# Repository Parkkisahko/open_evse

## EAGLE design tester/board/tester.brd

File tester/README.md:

# Basics
This testing library contains both an Arduino sketch, an example schema and python test cases to test relay and PWM timings to match 

# Python tests
## Setup
- Install pip first. ´sudo apt-get install python3-pip´
- Setup virtual environment: ´virtualenv -p python3 _py_env´
- Activate virtual environment: ´source _py_env/bin/activate´
- Install packages: ´pip install -r requirements.txt´

## Running tests
- Identify the serial ports used for both Arduino (testing device) and OpenEVSE
-- On OS X and Linux: ´ls /dev/tty*´
-- Replace OPEN_EVSE_PORT and TESTER_PORT with the correct ports in test.py
- Run tests by entering ´python test.py´

## Test cases
- TBD

# OpenEVSE tester
## Notes
- The schema provided is sensitive to board voltage due to selected optocoupler components not fully saturating at voltages below 5 V
- To overcome this issue, use a separate power supply for the Arduino

## Possible improvements
- Change optos to transistors
- Measure voltage at PWM high and low state
- Add circuits and corresponding code to provide for following automated test cases:
-- Diode check fail
-- Ground check fail
-- Stuck relay check (NOTE: Requires high voltages on board!)

# License
Open EVSE tester is licensed under the GNU license.
Copyright 2019 Santeri Oksanen / Parking Energy Ltd

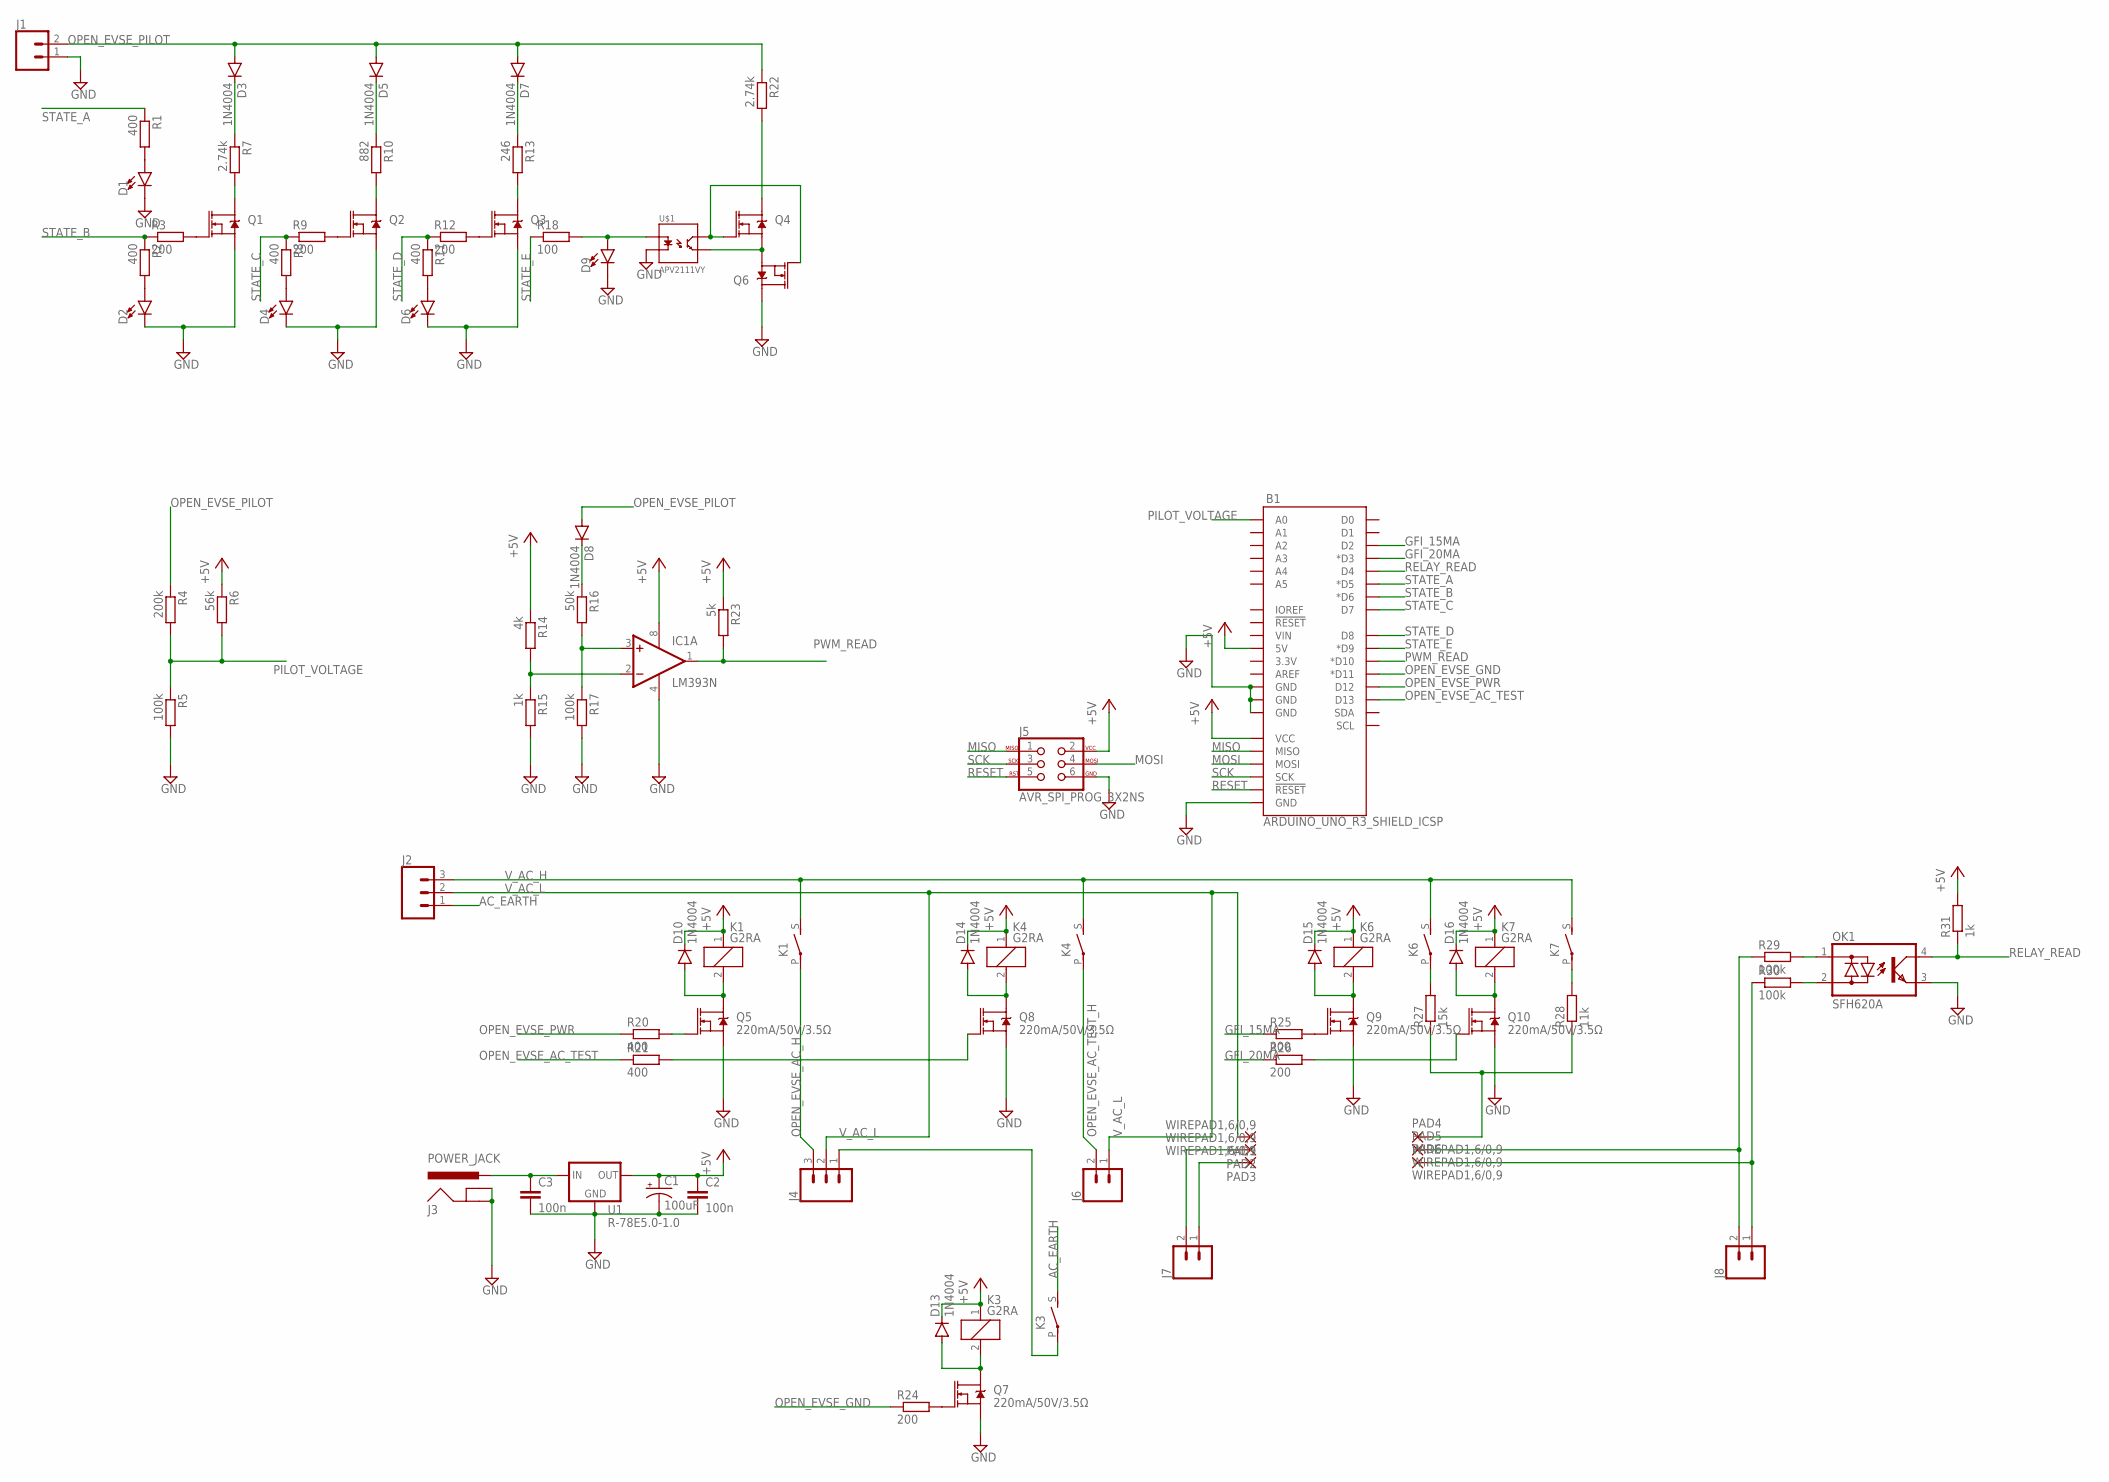
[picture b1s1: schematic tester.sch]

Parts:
B1: ARDUINO_UNO_R3_SHIELD_ICSP; UNO_R3_SHIELD_ICSP
C1: 100uF; CPOL-RADIAL-2.5MM-6.5MM
C2, C3: 100n; C025-024X044
D1, D2, D4, D6, D9: LED-FKIT-1206; FKIT-LED-1206
D3, D5, D7, D8, D10, D13, D14, D15, D16: 1N4004; DO41-10
IC1: LM393N; DIL08
J1, J6, J7, J8: CONN_023.5MM; SCREWTERMINAL-3.5MM-2
J2, J4: CONN_03-SCREW-5MM; SCREWTERMINAL-5MM-3
J3: POWER_JACK; POWER_JACK_PTH
J5: AVR_SPI_PROG_3X2NS; 2X3-NS
K1, K3, K4, K6, K7: G2RA
OK1: SFH620A; DIL04
PAD1, PAD2, PAD3, PAD4, PAD5, PAD6: WIREPAD1,6/0,9; 1,6/0,9
Q1, Q2, Q3, Q4, Q5, Q6, Q7, Q8, Q9, Q10: 220mA/50V/3.5Ω; SOT23-3
R1, R2, R8, R11, R20, R21: 400; R1206
R3, R9, R12, R24, R25, R26: 200; R1206
R4: 200k; R1206
R5, R17: 100k; R1206
R6: 56k; R1206
R7, R22: 2.74k; R1206
R10: 882; R1206
R13: 246; R1206
R14: 4k; R1206
R15, R31: 1k; R1206
R16: 50k; R1206
R18: 100; R1206
R23: 5k; R1206
R27: 15k; 0204/5
R28: 11k; 0204/5
R29, R30: 100k; 0204/5
U1: R-78E5.0-1.0; DC-DC_CONVERTER_78XX
U$1: APV2111VY; SSOP4

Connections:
+5V: B1.5V, B1.5V_ICSP (VCC), C1.1 (+), C2.1, D10.C, D13.C, D14.C, D15.C, D16.C, IC1.8 (V+), J5.2, K1.1, K3.1, K4.1, K6.1, K7.1, R6.1, R14.1, R23.1, R31.2, U1.VOUT (OUT)
AC_EARTH: J2.1, K3.S
GFI_15MA: B1.D2, R25.1
GFI_20MA: B1.D3 (*D3), R26.1
GND: B1.GND@0 (GND), B1.GND@1 (GND), B1.GND@2 (GND), B1.GND_ICSP (GND), C1.2 (-), C2.2, C3.2, D1.C, D2.C, D4.C, D6.C, D9.C, IC1.4 (V-), J1.1, J3.GND, J3.GNDBREAK, J5.6, OK1.3 (E), Q1.2 (S), Q2.2 (S), Q3.2 (S), Q5.2 (S), Q6.3 (D), Q7.2 (S), Q8.2 (S), Q9.2 (S), Q10.2 (S), R5.2, R15.2, R17.2, U1.GND, U$1.2 (C1)
MISO: B1.MISO, J5.1
MOSI: B1.MOSI, J5.4
unnamed: Q1.1 (G), R3.2
unnamed: D2.A, R2.2
unnamed: D3.C, R7.1
unnamed: Q2.1 (G), R9.2
unnamed: D6.A, R11.2
unnamed: Q3.1 (G), R12.2
unnamed: D7.C, R13.1
unnamed: Q3.3 (D), R13.2
unnamed: J7.1, PAD3.1
unnamed: IC1.2 (-IN), R14.2, R15.1
unnamed: Q1.3 (D), R7.2
unnamed: IC1.3 (+IN), R16.2, R17.1
unnamed: D8.C, R16.1
unnamed: Q4.2 (S), Q6.2 (S), U$1.4 (EM1)
unnamed: J7.2, PAD2.1
unnamed: Q4.3 (D), R22.2
unnamed: J4.1, K3.P
unnamed: J8.2, PAD5.1, R29.1
unnamed: J8.1, PAD6.1, R30.1
unnamed: OK1.1 (AC1), R29.2
unnamed: OK1.2 (AC2), R30.2
unnamed: C3.1, J3.PWR, U1.VIN (IN)
unnamed: D15.A, K6.2, Q9.3 (D)
unnamed: D4.A, R8.2
unnamed: D16.A, K7.2, Q10.3 (D)
unnamed: K7.P, R28.2
unnamed: Q8.1 (G), R21.2
unnamed: K6.P, R27.2
unnamed: PAD4.1, R27.1, R28.1
unnamed: D14.A, K4.2, Q8.3 (D)
unnamed: Q2.3 (D), R10.2
unnamed: D10.A, K1.2, Q5.3 (D)
unnamed: Q5.1 (G), R20.2
unnamed: D5.C, R10.1
unnamed: Q9.1 (G), R25.2
unnamed: Q10.1 (G), R26.2
unnamed: D1.A, R1.2
unnamed: D9.A, R18.2, U$1.1 (A1)
unnamed: Q7.1 (G), R24.2
unnamed: D13.A, K3.2, Q7.3 (D)
unnamed: Q4.1 (G), Q6.1 (G), U$1.3 (CL1)
OPEN_EVSE_AC_H: J4.3, K1.P
OPEN_EVSE_AC_TEST: B1.D13, R21.1
OPEN_EVSE_AC_TEST_H: J6.2, K4.P
OPEN_EVSE_GND: B1.D11 (*D11), R24.1
OPEN_EVSE_PILOT: D3.A, D5.A, D7.A, D8.A, J1.2, R4.1, R22.1
OPEN_EVSE_PWR: B1.D12, R20.1
PILOT_VOLTAGE: B1.A0, R4.2, R5.1, R6.2
PWM_READ: B1.D10 (*D10), IC1.1 (OUT), R23.2
RELAY_READ: B1.D4, OK1.4 (C), R31.1
RESET: B1.RST_ICSP (!RESET!), J5.5
SCK: B1.SCK, J5.3
STATE_A: B1.D5 (*D5), R1.1
STATE_B: B1.D6 (*D6), R2.1, R3.1
STATE_C: B1.D7, R8.1, R9.1
STATE_D: B1.D8, R11.1, R12.1
STATE_E: B1.D9 (*D9), R18.1
V_AC_H: J2.3, K1.S, K4.S, K6.S, K7.S
V_AC_L: J2.2, J4.2, J6.1, PAD1.1

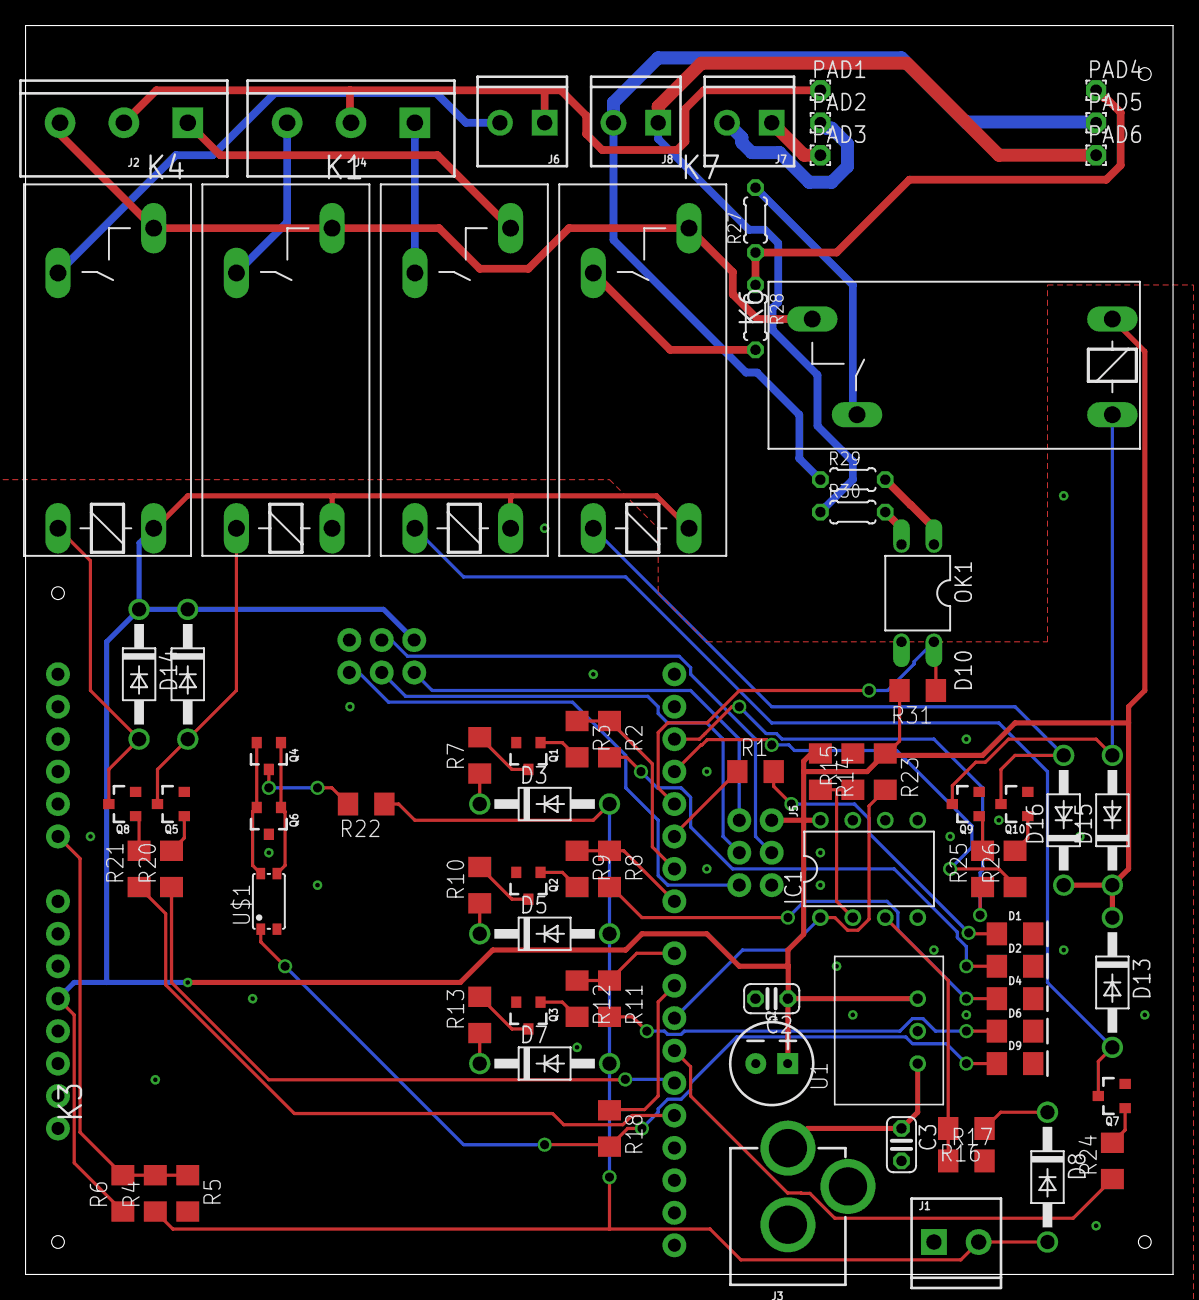
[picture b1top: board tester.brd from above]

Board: 2 copper layers, 89.8 x 97.8 mm, 81 parts (1 on the bottom side), 66 nets.

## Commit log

2019-03-08 Started work with tester
2019-03-11 Tester should be ready for testing
2019-03-11 Started with python tester
2019-03-11 Continuing with python tests
2019-03-12 First python tests against spec
2019-03-12 Test cases against default open_evse
2019-03-12 First try with possibility to disable pwm
2019-03-13 Added readme
2019-03-13 Tester schematics
2019-03-13 Improved schematic
2019-03-22 Tester schema and board
2019-08-16 Small changes
2019-08-16 Removed vscode settings from branch
2019-08-16 Added flashing script, prebuilt binaries
2019-08-16 Renamed readme
2019-08-16 Updated readmi
2019-08-16 Corrected fuses to enable bootloader
2019-08-16 flash.sh executable, updated readme
2019-09-05 V5.2.0, can use volatile amps, stores zero amps in eeprom
2019-09-05 Compiled binaries
2019-09-06 Respect zero amps upon startup

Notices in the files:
parts and their libraries:
SparkFun-Boards: Licensing: Creative Commons ShareAlike 4.0 International - https://creativecommons.org/licenses/by-sa/4.0
